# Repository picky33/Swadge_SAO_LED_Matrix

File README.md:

# Swadge_SAO_LED_Matrix
# Swadge_SAO_LED_Matrix

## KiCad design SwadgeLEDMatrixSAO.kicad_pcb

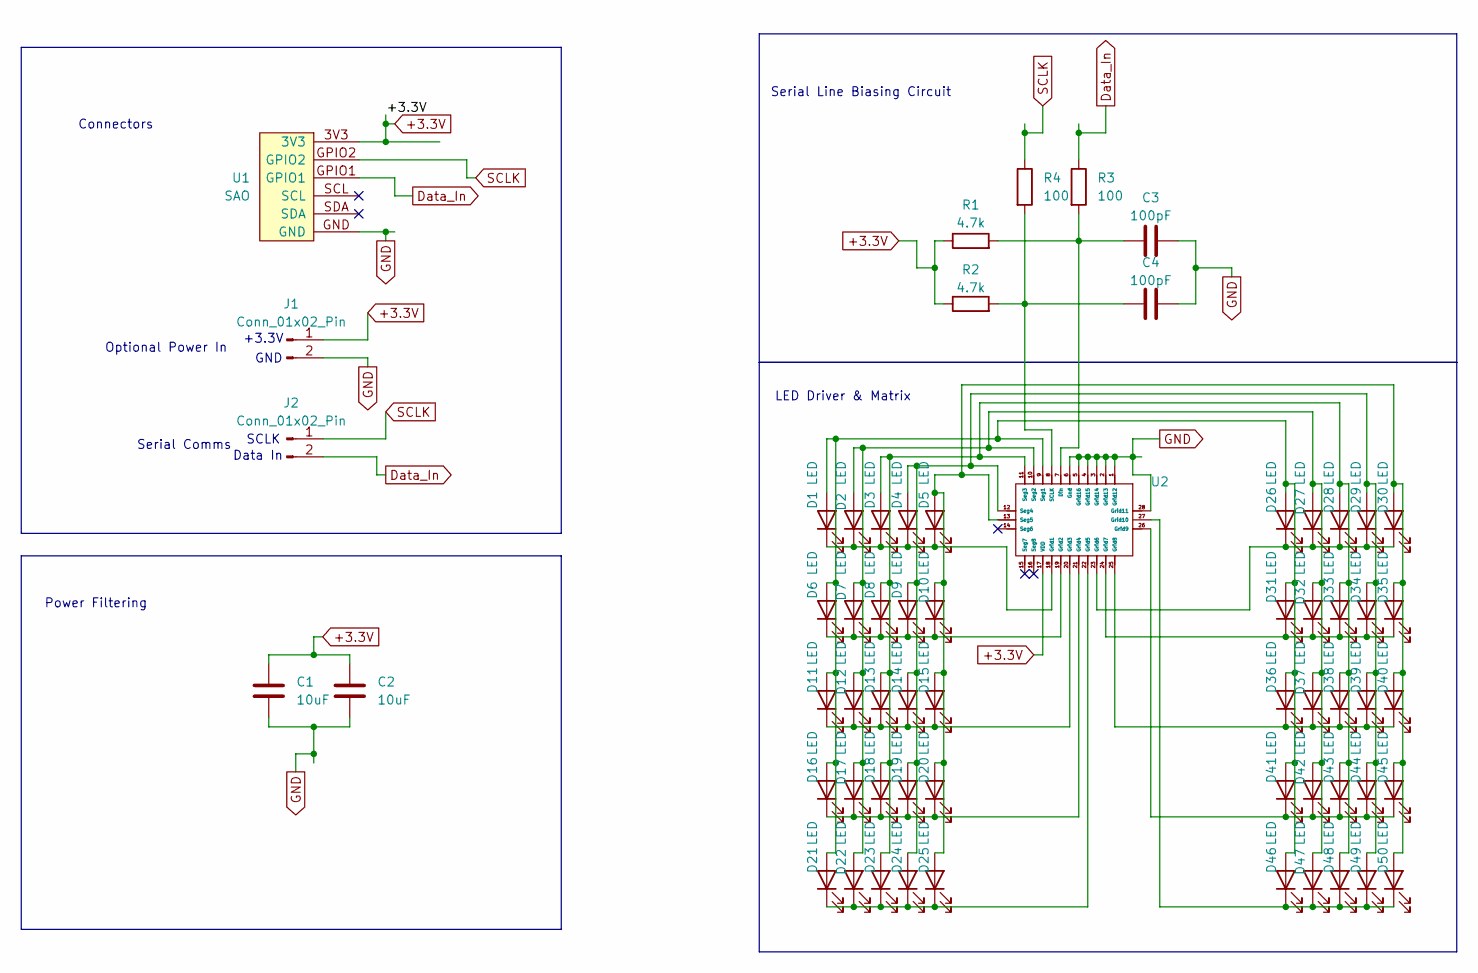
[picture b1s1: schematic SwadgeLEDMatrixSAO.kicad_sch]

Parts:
C1, C2: 10uF; C_0805_2012Metric_Pad1.18x1.45mm_HandSolder
C3, C4: 100pF; C_0805_2012Metric_Pad1.18x1.45mm_HandSolder
D1, D2, D3, D4, D5, D6, D7, D8, D9, D10, D11, D12, D13, D14, D15, D16, D17, D18, D19, D20, D21, D22, D23, D24, D25, D26, D27, D28, D29, D30, D31, D32, D33, D34, D35, D36, D37, D38, D39, D40, D41, D42, D43, D44, D45, D46, D47, D48, D49, D50: LED; LED_0603_1608Metric_Pad1.05x0.95mm_HandSolder
J1, J2: Conn_01x02_Pin; PinHeader_1x02_P2.54mm_Vertical
R1, R2: 4.7k; R_0805_2012Metric_Pad1.20x1.40mm_HandSolder
R3, R4: 100; R_0805_2012Metric_Pad1.20x1.40mm_HandSolder
U1: SAO; Digikey n/a
U2: EP1640

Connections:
+3.3V: C1.1, C2.1, J1.1, R1.1, R2.1, U1.3V3, U2.17 (VDD)
Data_In: J2.2, R3.1, U1.GPIO1
GND: C1.2, C2.2, C3.2, C4.2, J1.2, U1.GND, U2.1 (Grid12), U2.2 (Grid13), U2.3 (Grid14), U2.4 (Grid15), U2.5 (Grid16), U2.6 (Gnd), U2.28 (Grid11)
unnamed: D1.2 (A), D6.2 (A), D11.2 (A), D16.2 (A), D21.2 (A), D26.2 (A), D31.2 (A), D36.2 (A), D41.2 (A), D46.2 (A), U2.9 (Seg1)
unnamed: D1.1 (K), D2.1 (K), D3.1 (K), D4.1 (K), D5.1 (K), U2.18 (Grid1)
unnamed: D5.2 (A), D10.2 (A), D15.2 (A), D20.2 (A), D25.2 (A), D30.2 (A), D35.2 (A), D40.2 (A), D45.2 (A), D50.2 (A), U2.13 (Seg5)
unnamed: D6.1 (K), D7.1 (K), D8.1 (K), D9.1 (K), D10.1 (K), U2.19 (Grid2)
unnamed: D11.1 (K), D12.1 (K), D13.1 (K), D14.1 (K), D15.1 (K), U2.20 (Grid3)
unnamed: D2.2 (A), D7.2 (A), D12.2 (A), D17.2 (A), D22.2 (A), D27.2 (A), D32.2 (A), D37.2 (A), D42.2 (A), D47.2 (A), U2.10 (Seg2)
unnamed: D3.2 (A), D8.2 (A), D13.2 (A), D18.2 (A), D23.2 (A), D28.2 (A), D33.2 (A), D38.2 (A), D43.2 (A), D48.2 (A), U2.11 (Seg3)
unnamed: D4.2 (A), D9.2 (A), D14.2 (A), D19.2 (A), D24.2 (A), D29.2 (A), D34.2 (A), D39.2 (A), D44.2 (A), D49.2 (A), U2.12 (Seg4)
unnamed: D16.1 (K), D17.1 (K), D18.1 (K), D19.1 (K), D20.1 (K), U2.21 (Grid4)
unnamed: D21.1 (K), D22.1 (K), D23.1 (K), D24.1 (K), D25.1 (K), U2.22 (Grid5)
unnamed: D26.1 (K), D27.1 (K), D28.1 (K), D29.1 (K), D30.1 (K), U2.23 (Grid6)
unnamed: D31.1 (K), D32.1 (K), D33.1 (K), D34.1 (K), D35.1 (K), U2.24 (Grid7)
unnamed: D36.1 (K), D37.1 (K), D38.1 (K), D39.1 (K), D40.1 (K), U2.25 (Grid8)
unnamed: D41.1 (K), D42.1 (K), D43.1 (K), D44.1 (K), D45.1 (K), U2.26 (Grid9)
unnamed: D46.1 (K), D47.1 (K), D48.1 (K), D49.1 (K), D50.1 (K), U2.27 (Grid10)
unnamed: C3.1, R1.2, R3.2, U2.7 (Din)
unnamed: C4.1, R2.2, R4.2, U2.8 (SCLK)
SCLK: J2.1, R4.1, U1.GPIO2

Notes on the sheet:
Data In
GND
Serial Line Biasing Circuit
SCLK
Power Filtering
Connectors
Serial Comms
Optional Power In
LED Driver & Matrix
+3.3V

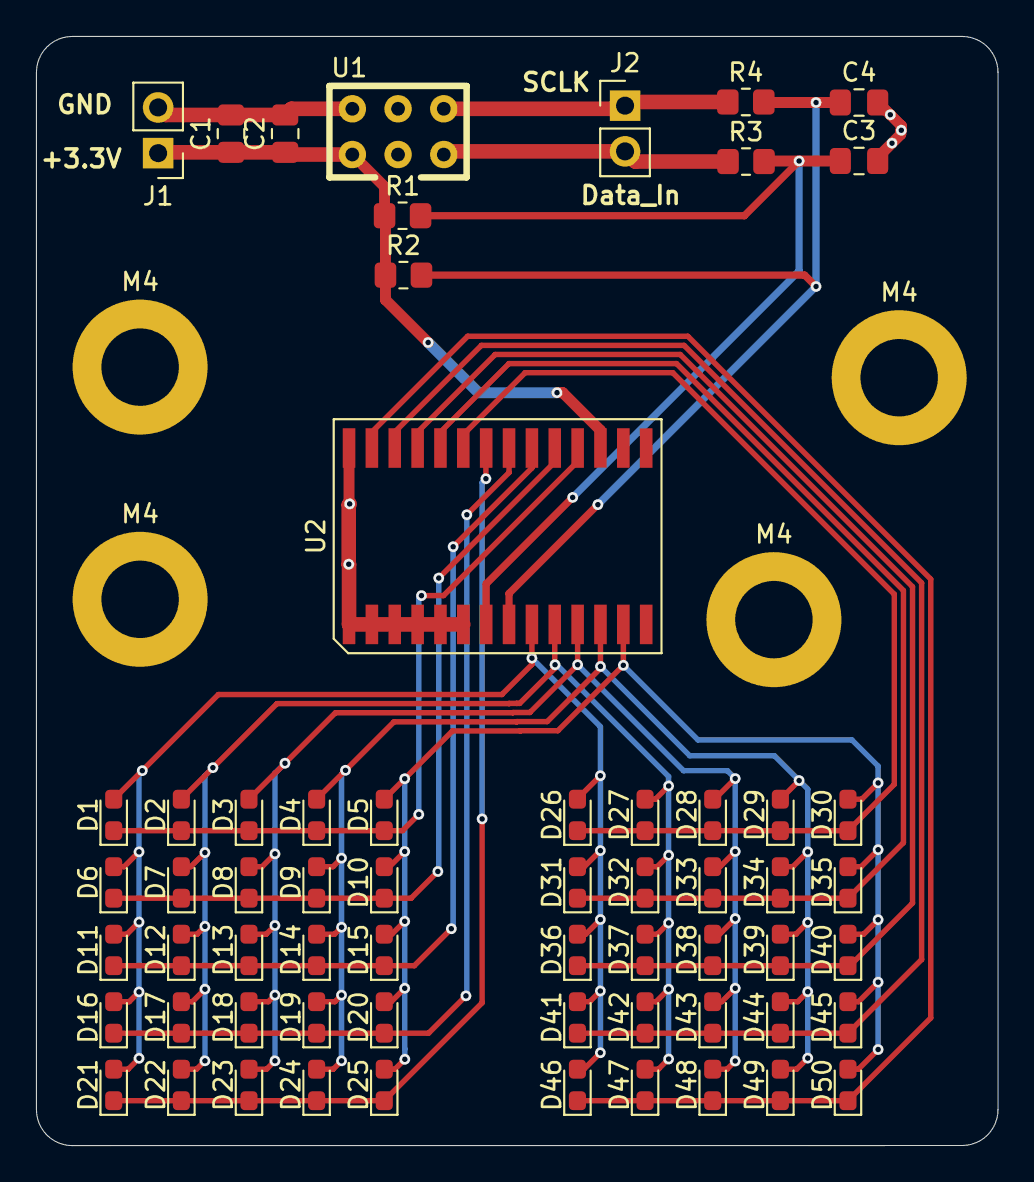
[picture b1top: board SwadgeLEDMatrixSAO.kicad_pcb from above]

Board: 2 copper layers, 53.4 x 61.6 mm, 66 parts (0 on the bottom side), 21 nets.

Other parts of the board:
M4, M4#2, M4#3, M4#4: MountingHole_4.3mm_M4_DIN965_Pad

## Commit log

2025-05-12 Added Pictures
    Pictures
